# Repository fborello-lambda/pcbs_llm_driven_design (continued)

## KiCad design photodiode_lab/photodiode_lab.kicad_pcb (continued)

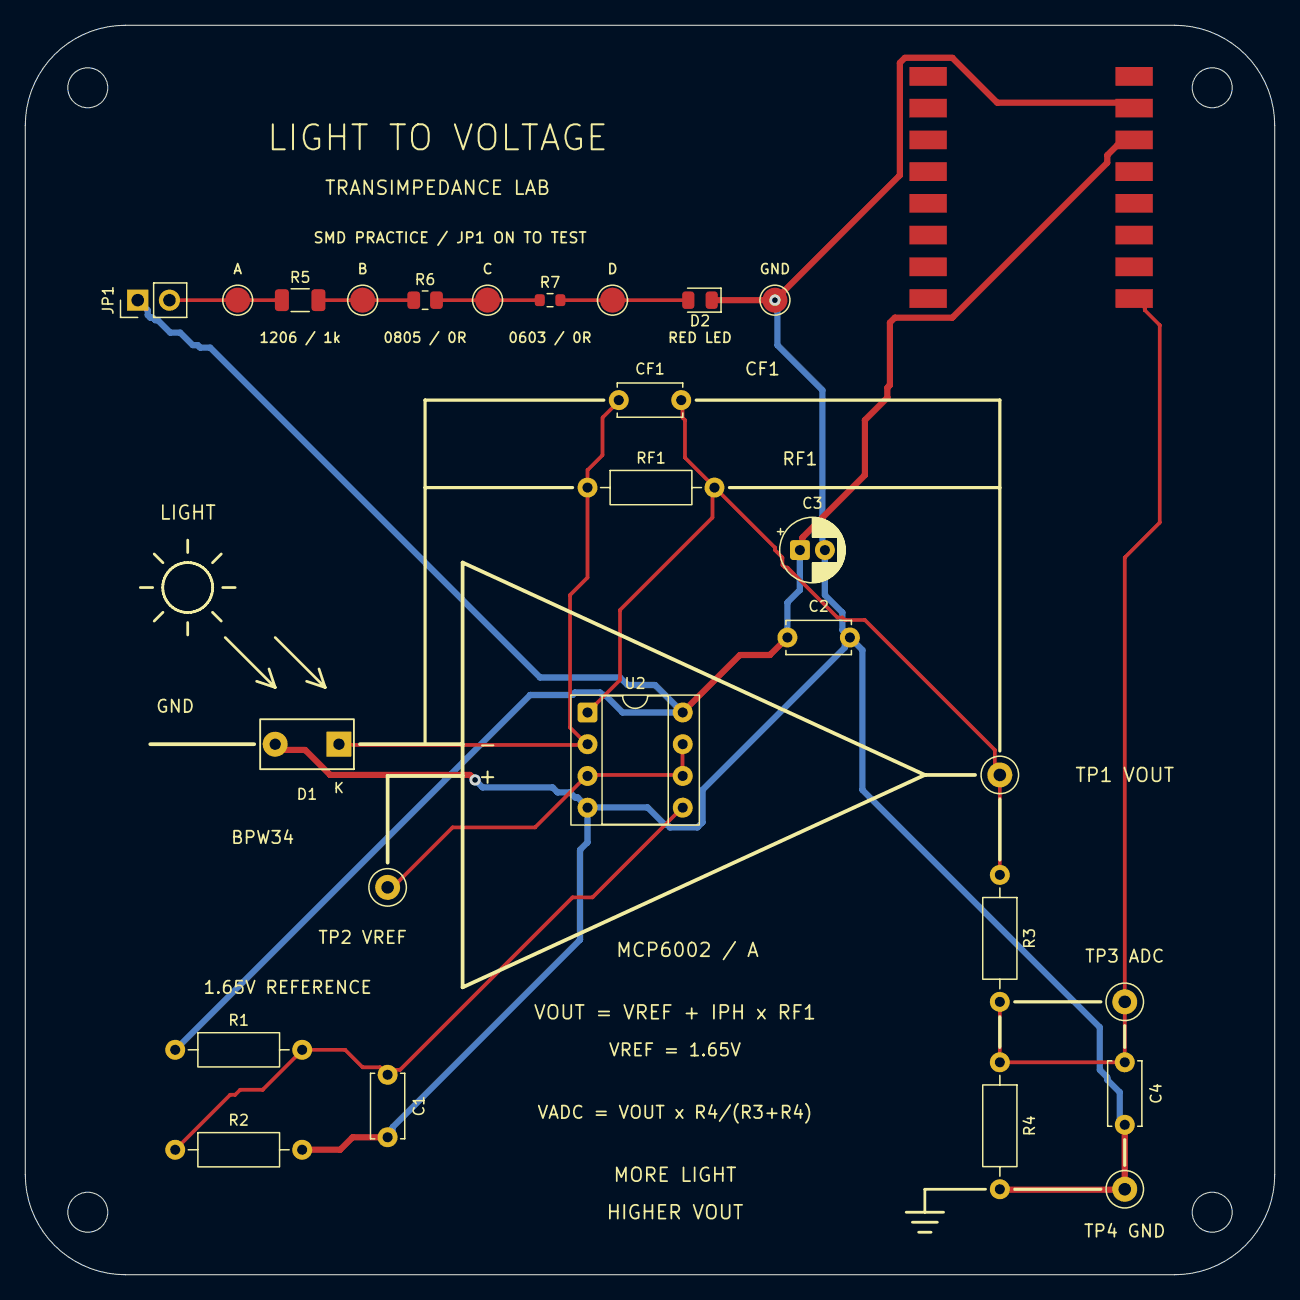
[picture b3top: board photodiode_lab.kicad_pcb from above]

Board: 2 copper layers, 100.0 x 100.0 mm, 31 parts (0 on the bottom side), 11 nets.

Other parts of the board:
H1, H2, H3, H4: MountingHole_3.2mm_M3

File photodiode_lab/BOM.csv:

Reference,Value,Footprint,Notes
U1,ESP32-C3 SuperMini,Shared:ESP32-C3-SuperMini,Shared direct-solder landing pattern. USB at top edge; antenna keepout x70..90 y24.7..38. GPIO0 ADC1.
U2,MCP6002-I/P,Package_DIP:DIP-8_W7.62mm_Socket,"DIP8: A=transimpedance; B=reference buffer. 1 MHz, RRIO, 1.8-6V supply."
D1,BPW34,Lab:BPW34_Vishay,Vishay drawing 96 12186: 5.1mm pitch. Pad1 cathode to SUM (right); pad2 anode to GND (left). More light raises VOUT.
RF1,100k 1%,Resistor_THT:R_Axial_DIN0207_L6.3mm_D2.5mm_P10.16mm_Horizontal,"Standard soldered axial resistor, 10.16mm pitch. Start at 100k; any later variable-resistance arrangement is user-defined."
CF1,1n C0G,Capacitor_THT:C_Disc_D5.0mm_W2.5mm_P5.00mm,Fixed feedback compensation. For low-speed teaching; 159Hz at RF=1M.
R1,10k 1%,Resistor_THT:R_Axial_DIN0207_L6.3mm_D2.5mm_P10.16mm_Horizontal,
R2,10k 1%,Resistor_THT:R_Axial_DIN0207_L6.3mm_D2.5mm_P10.16mm_Horizontal,
C1,100n,Capacitor_THT:C_Disc_D5.0mm_W2.5mm_P5.00mm,
C2,100n,Capacitor_THT:C_Disc_D5.0mm_W2.5mm_P5.00mm,Local supply bypass next to U2 pin8; THT ceramic.
C3,10u / 10V,Capacitor_THT:CP_Radial_D5.0mm_P2.00mm,
R3,10k 1%,Resistor_THT:R_Axial_DIN0207_L6.3mm_D2.5mm_P10.16mm_Horizontal,ADC divider top; protect useful ADC range even if VOUT saturates high.
R4,22k 1%,Resistor_THT:R_Axial_DIN0207_L6.3mm_D2.5mm_P10.16mm_Horizontal,
C4,100n,Capacitor_THT:C_Disc_D5.0mm_W2.5mm_P5.00mm,
TP1,VOUT,TestPoint:TestPoint_Loop_D2.50mm_Drill1.0mm,Accessible multimeter/scope point. Do not probe the sensitive SUM node.
TP2,VREF,TestPoint:TestPoint_Loop_D2.50mm_Drill1.0mm,Accessible multimeter/scope point. Do not probe the sensitive SUM node.
TP3,ADC_OUT,TestPoint:TestPoint_Loop_D2.50mm_Drill1.0mm,Accessible multimeter/scope point. Do not probe the sensitive SUM node.
TP4,GND,TestPoint:TestPoint_Loop_D2.50mm_Drill1.0mm,Accessible multimeter/scope point. Do not probe the sensitive SUM node.
JP1,PRACTICE ENABLE,Connector_PinHeader_2.54mm:PinHeader_1x02_P2.54mm_Vertical,Normally open. Fit a shunt only after checking the practice circuit; remove during TIA measurements.
R5,1k,Resistor_SMD:R_1206_3216Metric,Optional soldering practice. R5 limits LED current; R6/R7 are zero-ohm assembly exercises.
R6,0R,Resistor_SMD:R_0805_2012Metric,Optional soldering practice. R5 limits LED current; R6/R7 are zero-ohm assembly exercises.
R7,0R,Resistor_SMD:R_0603_1608Metric,Optional soldering practice. R5 limits LED current; R6/R7 are zero-ohm assembly exercises.
D2,RED,LED_SMD:LED_0805_2012Metric,Optional red LED. Cathode K on the right. About 1-2mA with 3.3V and R5=1k; no firmware required.

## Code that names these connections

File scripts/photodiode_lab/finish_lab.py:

#!/usr/bin/python3
"""Check source geometry, synchronize KiCad no-connect nets, and prove netlist parity."""
from pathlib import Path
import json, xml.etree.ElementTree as ET
import pcbnew as p
ROOT=Path(__file__).resolve().parents[2]/'photodiode_lab'
b=p.LoadBoard(str(ROOT/'photodiode_lab.kicad_pcb'))
fps={f.GetReference():f for f in b.GetFootprints()}
xml=ET.parse(ROOT/'outputs/netlist.xml')
nets={n.GetNetname():n for n in b.GetNetsByNetcode().values()}
for n in xml.findall('.//nets/net'):
    name=n.get('name')
    if not name.startswith('unconnected-'):continue
    if name not in nets:nets[name]=p.NETINFO_ITEM(b,name);b.Add(nets[name])
    for node in n.findall('node'):
        for pad in fps[node.get('ref')].Pads():
            if pad.GetNumber()==node.get('pin'):pad.SetNet(nets[name])
parts=json.loads((ROOT/'connectivity.json').read_text())
expected={(c['ref'],pin):'/'+net for c in parts for pin,net in c['nets'].items()}
actual={(f.GetReference(),z.GetNumber()):z.GetNetname() for f in b.GetFootprints() for z in f.Pads() if z.GetNetname() and not z.GetNetname().startswith('unconnected-')}
schematic={(node.get('ref'),node.get('pin')):n.get('name') for n in xml.findall('.//nets/net') for node in n.findall('node') if (node.get('ref'),node.get('pin')) in expected}
assert expected==actual==schematic
pinmap={1:'/VOUT',2:'/SUM',3:'/VREF',4:'/GND',5:'/REF_DIV',6:'/VREF',7:'/VREF',8:'/+3V3'}
assert {int(z.GetNumber()):z.GetNetname() for z in fps['U2'].Pads()}==pinmap
assert {int(z.GetNumber()):z.GetNetname() for z in fps['D1'].Pads()}=={1:'/SUM',2:'/GND'}
def pattern(f):return sorted((z.GetNumber(),z.GetFPRelativePosition().x,z.GetFPRelativePosition().y,z.GetSize().x,z.GetSize().y,z.GetAttribute()) for z in f.Pads())
assert pattern(fps['U1'])==pattern(p.FootprintLoad(str(ROOT.parent/'shared/ESP32-C3-SuperMini.pretty'),'ESP32-C3-SuperMini'))
practice_refs={'JP1','R5','R6','R7','D2','TP5','TP6','TP7','TP8','TP9'}
assert all(z.GetNetname() not in ['/SUM','/VREF','/REF_DIV','/ADC_OUT','/VOUT'] for ref in practice_refs for z in fps[ref].Pads())
assert fps['R5'].GetValue()=='1k'
# Approximate bodies for parts without installed vendor CAD, plus IC in its socket.
models=ROOT/'libraries/3d';models.mkdir(exist_ok=True)
def box(x,y,z,a,b,c,color):
    return f'Transform {{ translation {x/2.54} {y/2.54} {z/2.54} children [ Shape {{ appearance Appearance {{ material Material {{ diffuseColor {color} }} }} geometry Box {{ size {a/2.54} {b/2.54} {c/2.54} }} }} ] }}\n'
header='#VRML V2.0 utf8\n# Approximate visual envelope, not manufacturer CAD.\n'
(models/'bpw34-envelope.wrl').write_text(header+box(2.55,0,2.6,5.4,4.3,3.2,'.25 .16 .12')+box(2.55,0,4.23,3,2.5,.08,'.03 .03 .04'))
for ref,filename in [('D1','bpw34-envelope.wrl')]:
    local=p.FootprintLoad(str(ROOT/'libraries/Lab.pretty'),ref)
    for obj in [fps[ref],local]:
        obj.Models().clear();model=p.FP_3DMODEL();model.m_Filename='${KIPRJMOD}/libraries/3d/'+filename;obj.Add3DModel(model)
    p.FootprintSave(str(ROOT/'libraries/Lab.pretty'),local)
local=p.FootprintLoad(str(ROOT/'libraries/Lab.pretty'),'U2')
for obj in [fps['U2'],local]:
    keep=[m for m in obj.Models() if not m.m_Filename.endswith('/DIP-8_W7.62mm.step')];obj.Models().clear()
    for m in keep:obj.Add3DModel(m)
    m=p.FP_3DMODEL();m.m_Filename='${KICAD10_3DMODEL_DIR}/Package_DIP.3dshapes/DIP-8_W7.62mm.step';m.m_Offset=p.VECTOR3D(0,0,3);obj.Add3DModel(m)
p.FootprintSave(str(ROOT/'libraries/Lab.pretty'),local)
p.SaveBoard(str(ROOT/'photodiode_lab.kicad_pcb'),b)
report=dict(matched_pins=len(expected),schematic_matches_pcb=True,mcp6002_datasheet_pinout=True,bpw34_cathode_to_sum_anode_to_gnd=True,output_increases_with_light=True,esp32_matches_shared_footprint=True)
(ROOT/'outputs/verification.json').write_text(json.dumps(report,indent=2));print(report)

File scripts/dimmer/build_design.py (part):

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parts=[]
def add(ref,lib,value,fp,nets,sch,pcb,notes=''):
    parts.append(dict(ref=ref,lib=lib,value=value,fp=fp,nets={str(k):v for k,v in nets.items()},sch=sch,pcb=pcb,notes=notes))
add('U1','ESP32C3_SuperMini:ESP32-C3-SuperMini','ESP32-C3 SuperMini','Shared:ESP32-C3-SuperMini',{2:'SDA',3:'SCL',12:'ZC',13:'FIRE',14:'+3V3',15:'GND'},(100,55),(49.495,14,0),'External 3.3 V supply for the ESP32. GPIO5 is unused; no relay or auxiliary supply. Shared direct-solder footprint.')
add('J1','Connector_Generic:Conn_01x04','I2C CONTROL / 3V3','Connector_JST:JST_XH_B4B-XH-A_1x04_P2.50mm_Vertical',{1:'3V3_EXT',2:'GND',3:'SDA',4:'SCL'},(40,45),(12,16,0),'JST XH 2.50 mm: 1=3V3 input, 2=GND, 3=SDA, 4=SCL. Regulated SELV supply >=1 A; available capacity must be confirmed.')
add('JP1','Jumper:Jumper_2_Open','RUN / OPEN FOR USB','Connector_PinHeader_2.54mm:PinHeader_1x02_P2.54mm_Vertical',{1:'3V3_EXT',2:'+3V3'},(40,75),(29,17,0),'Fit shunt for normal use. Remove shunt and disconnect J1 before USB flashing.')
add('R3','Device:R','82R / 0.25W',Rsmall,{1:'+3V3',2:'OPTO_A'},(172.72,38.1),(65,15,0),'MOC3052 LED: approximately 19 to 25 mA nominal; driven by a transistor.')
add('U2','Relay_SolidState:MOC3052M','MOC3052M','Package_DIP:DIP-6_W10.16mm',{1:'OPTO_A',2:'OPTO_K',4:'GATE',6:'GATE_DRIVE'},(220.98,55.88),(72.54,32.92,270),'600 V random-phase optotriac. Do not substitute MOC306x/MOC304x. Leads formed to 10.16 mm.')
add('Q1','Transistor_BJT:BC547','BC547','Package_TO_SOT_THT:TO-92_Inline_Wide',{1:'OPTO_K',2:'BASE',3:'GND'},(185.42,73.66),(80,17,0),'C-B-E according to the selected manufacturer; verify purchased part pinout.')
add('R4','Device:R','1k / 0.25W',Rsmall,{1:'FIRE',2:'BASE'},(154.94,73.66),(66,25,0))
add('R5','Device:R','10k / 0.25W',Rsmall,{1:'BASE',2:'GND'},(172.72,96.52),(83,26,0),'Keeps the transistor off during reset.')
add('U3','Isolator:H11AA1','H11AA1',DIP,{1:'ZC_AC',2:'N',4:'GND',5:'ZC'},(220.98,132.08),(27.46,43.08,90),'Isolated AC zero-crossing detector. Leads formed to 10.16 mm; no socket.')
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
